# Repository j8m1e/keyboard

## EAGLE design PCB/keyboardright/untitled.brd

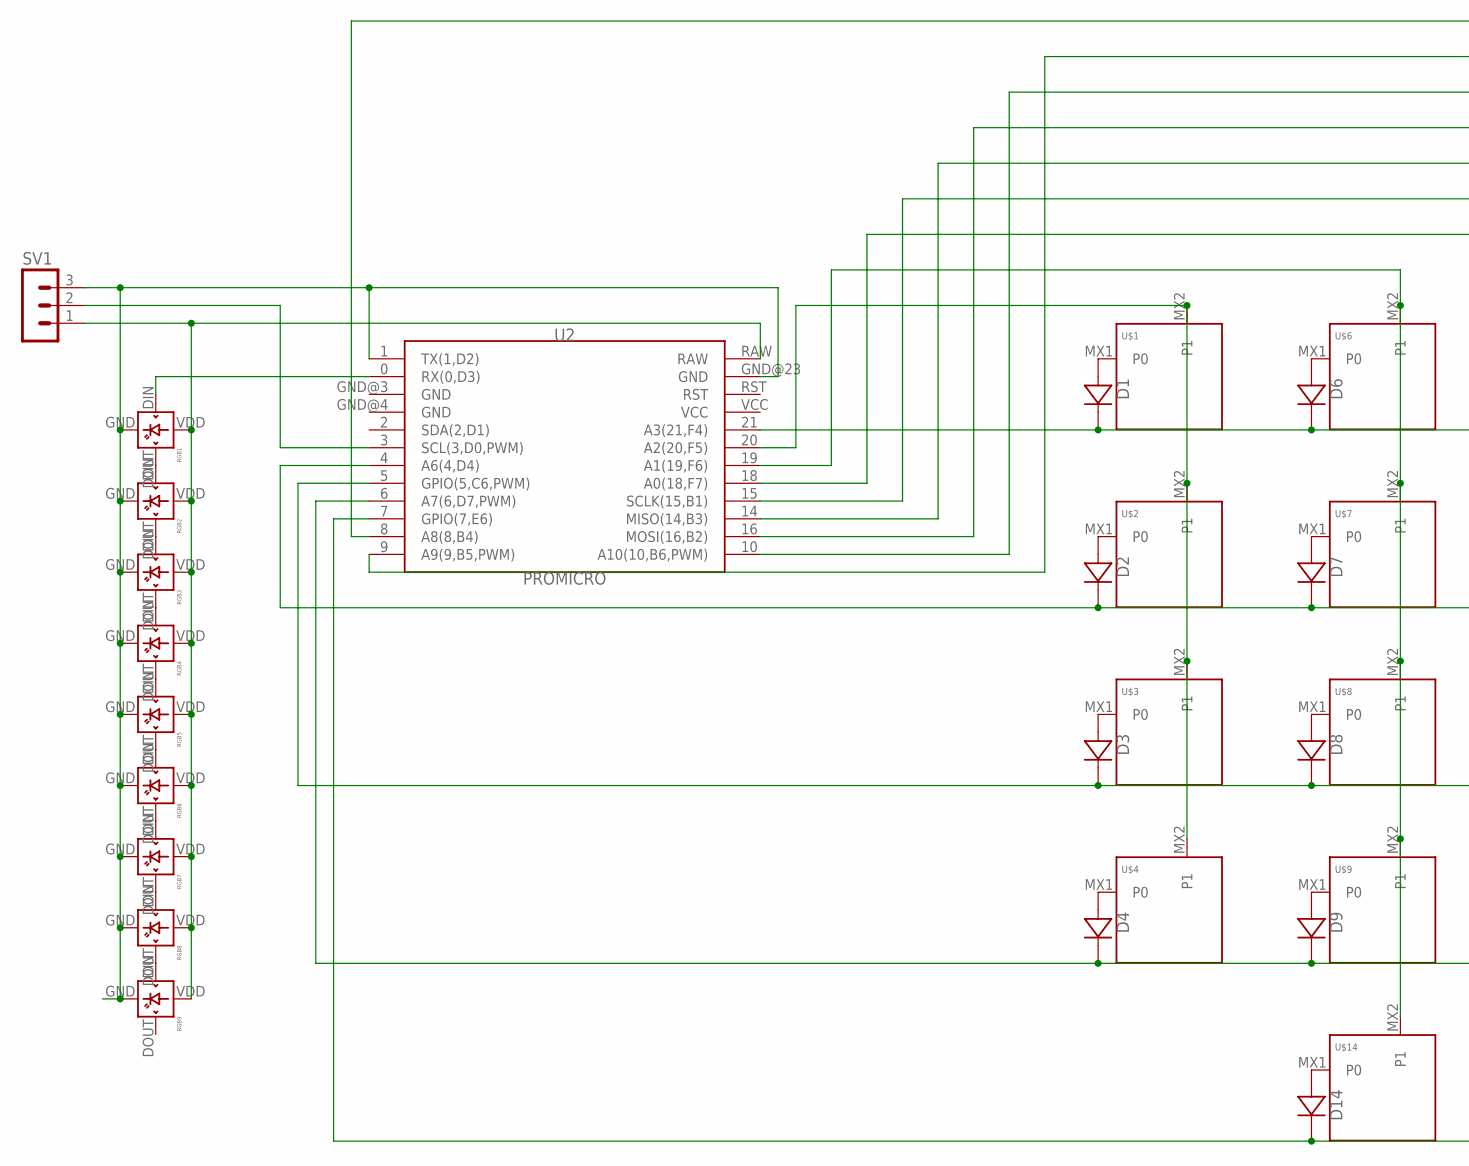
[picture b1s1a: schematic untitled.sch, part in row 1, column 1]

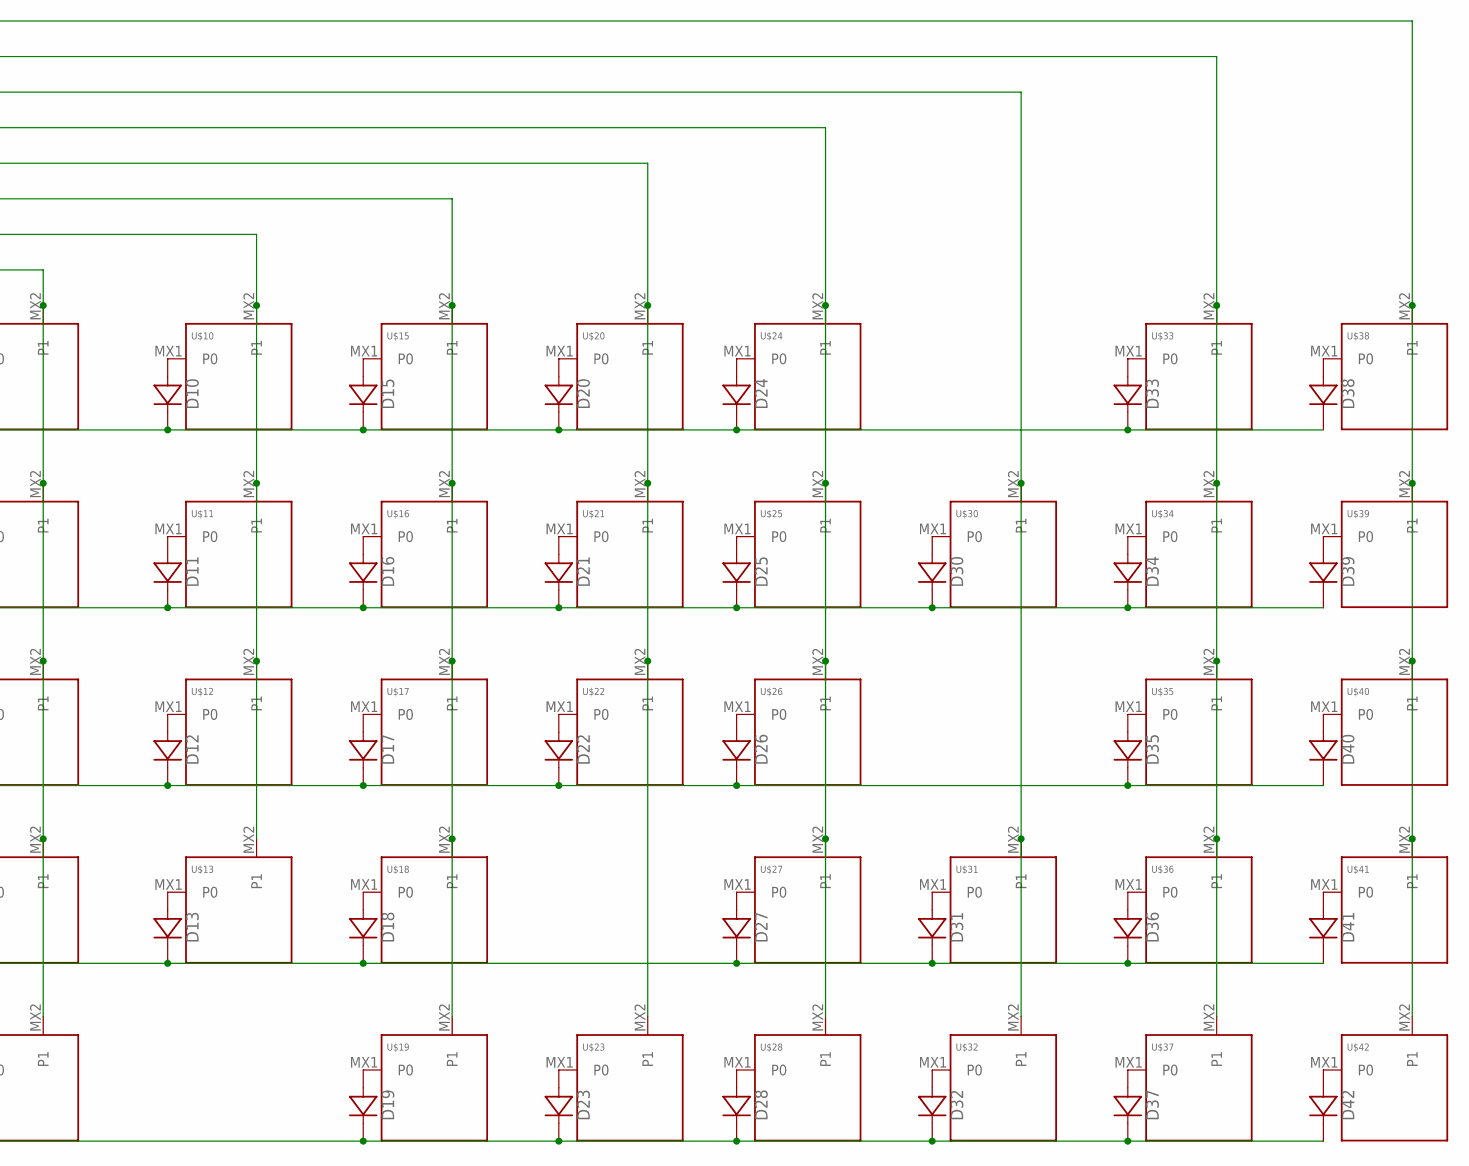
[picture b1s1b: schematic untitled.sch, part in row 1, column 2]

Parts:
D1, D2, D3, D4, D6, D7, D8, D9, D10, D11, D12, D13, D14, D15, D16, D17, D18, D19, D20, D21, D22, D23, D24, D25, D26, D27, D28, D30, D31, D32, D33, D34, D35, D36, D37, D38, D39, D40, D41, D42: DIODE-SOD-123; SOD-123
RGB1, RGB2, RGB3, RGB4, RGB5, RGB6, RGB7, RGB8, RGB9: WS2812B-MINI
SV1: MA03-1
U2: PROMICRO
U$1, U$2, U$3, U$4, U$6, U$7, U$8, U$9, U$10, U$11, U$12, U$13, U$14, U$15, U$16, U$17, U$18, U$19, U$20, U$21, U$22, U$23, U$24, U$25, U$26, U$27, U$28, U$30, U$31, U$32, U$33, U$34, U$35, U$36, U$37, U$38, U$39, U$40, U$41, U$42: KEYSWITCH-PLAIN-MX-1U; MX-1U

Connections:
unnamed: D1.A, U$1.MX1 (P0)
unnamed: D2.A, U$2.MX1 (P0)
unnamed: D3.A, U$3.MX1 (P0)
unnamed: D4.A, U$4.MX1 (P0)
unnamed: RGB1.DOUT, RGB2.DIN
unnamed: D6.A, U$6.MX1 (P0)
unnamed: D7.A, U$7.MX1 (P0)
unnamed: D8.A, U$8.MX1 (P0)
unnamed: D9.A, U$9.MX1 (P0)
unnamed: D10.A, U$10.MX1 (P0)
unnamed: D11.A, U$11.MX1 (P0)
unnamed: D12.A, U$12.MX1 (P0)
unnamed: D13.A, U$13.MX1 (P0)
unnamed: D14.A, U$14.MX1 (P0)
unnamed: D15.A, U$15.MX1 (P0)
unnamed: D16.A, U$16.MX1 (P0)
unnamed: D17.A, U$17.MX1 (P0)
unnamed: D18.A, U$18.MX1 (P0)
unnamed: D19.A, U$19.MX1 (P0)
unnamed: D20.A, U$20.MX1 (P0)
unnamed: D21.A, U$21.MX1 (P0)
unnamed: D22.A, U$22.MX1 (P0)
unnamed: D23.A, U$23.MX1 (P0)
unnamed: D24.A, U$24.MX1 (P0)
unnamed: D25.A, U$25.MX1 (P0)
unnamed: D26.A, U$26.MX1 (P0)
unnamed: D27.A, U$27.MX1 (P0)
unnamed: D28.A, U$28.MX1 (P0)
unnamed: RGB2.DOUT, RGB3.DIN
unnamed: D30.A, U$30.MX1 (P0)
unnamed: D31.A, U$31.MX1 (P0)
unnamed: D32.A, U$32.MX1 (P0)
unnamed: D33.A, U$33.MX1 (P0)
unnamed: D34.A, U$34.MX1 (P0)
unnamed: D35.A, U$35.MX1 (P0)
unnamed: D36.A, U$36.MX1 (P0)
unnamed: D37.A, U$37.MX1 (P0)
unnamed: D38.A, U$38.MX1 (P0)
unnamed: D39.A, U$39.MX1 (P0)
unnamed: D40.A, U$40.MX1 (P0)
unnamed: D41.A, U$41.MX1 (P0)
unnamed: D42.A, U$42.MX1 (P0)
unnamed: U2.20 (A2(20,F5)), U$1.MX2 (P1), U$2.MX2 (P1), U$3.MX2 (P1), U$4.MX2 (P1)
unnamed: U2.19 (A1(19,F6)), U$6.MX2 (P1), U$7.MX2 (P1), U$8.MX2 (P1), U$9.MX2 (P1), U$14.MX2 (P1)
unnamed: U2.18 (A0(18,F7)), U$10.MX2 (P1), U$11.MX2 (P1), U$12.MX2 (P1), U$13.MX2 (P1)
unnamed: U2.15 (SCLK(15,B1)), U$15.MX2 (P1), U$16.MX2 (P1), U$17.MX2 (P1), U$18.MX2 (P1), U$19.MX2 (P1)
unnamed: U2.14 (MISO(14,B3)), U$20.MX2 (P1), U$21.MX2 (P1), U$22.MX2 (P1), U$23.MX2 (P1)
unnamed: U2.16 (MOSI(16,B2)), U$24.MX2 (P1), U$25.MX2 (P1), U$26.MX2 (P1), U$27.MX2 (P1), U$28.MX2 (P1)
unnamed: U2.10 (A10(10,B6,PWM)), U$30.MX2 (P1), U$31.MX2 (P1), U$32.MX2 (P1)
unnamed: U2.9 (A9(9,B5,PWM)), U$33.MX2 (P1), U$34.MX2 (P1), U$35.MX2 (P1), U$36.MX2 (P1), U$37.MX2 (P1)
unnamed: D1.C, D6.C, D10.C, D15.C, D20.C, D24.C, D33.C, D38.C, U2.21 (A3(21,F4))
unnamed: D2.C, D7.C, D11.C, D16.C, D21.C, D25.C, D30.C, D34.C, D39.C, U2.4 (A6(4,D4))
unnamed: D3.C, D8.C, D12.C, D17.C, D22.C, D26.C, D35.C, D40.C, U2.5 (GPIO(5,C6,PWM))
unnamed: D4.C, D9.C, D13.C, D18.C, D27.C, D31.C, D36.C, D41.C, U2.6 (A7(6,D7,PWM))
unnamed: D14.C, D19.C, D23.C, D28.C, D32.C, D37.C, D42.C, U2.7 (GPIO(7,E6))
unnamed: U2.8 (A8(8,B4)), U$38.MX2 (P1), U$39.MX2 (P1), U$40.MX2 (P1), U$41.MX2 (P1), U$42.MX2 (P1)
unnamed: RGB3.DOUT, RGB4.DIN
unnamed: RGB4.DOUT, RGB5.DIN
unnamed: RGB5.DOUT, RGB6.DIN
unnamed: RGB6.DOUT, RGB7.DIN
unnamed: RGB7.DOUT, RGB8.DIN
unnamed: RGB8.DOUT, RGB9.DIN
unnamed: RGB1.VDD, RGB2.VDD, RGB3.VDD, RGB4.VDD, RGB5.VDD, RGB6.VDD, RGB7.VDD, RGB8.VDD, RGB9.VDD, SV1.1, U2.RAW
unnamed: RGB1.GND, RGB2.GND, RGB3.GND, RGB4.GND, RGB5.GND, RGB6.GND, RGB7.GND, RGB8.GND, RGB9.GND, SV1.3, U2.1 (TX(1,D2)), U2.GND@23 (GND)
unnamed: RGB1.DIN, U2.0 (RX(0,D3))
unnamed: SV1.2, U2.3 (SCL(3,D0,PWM))

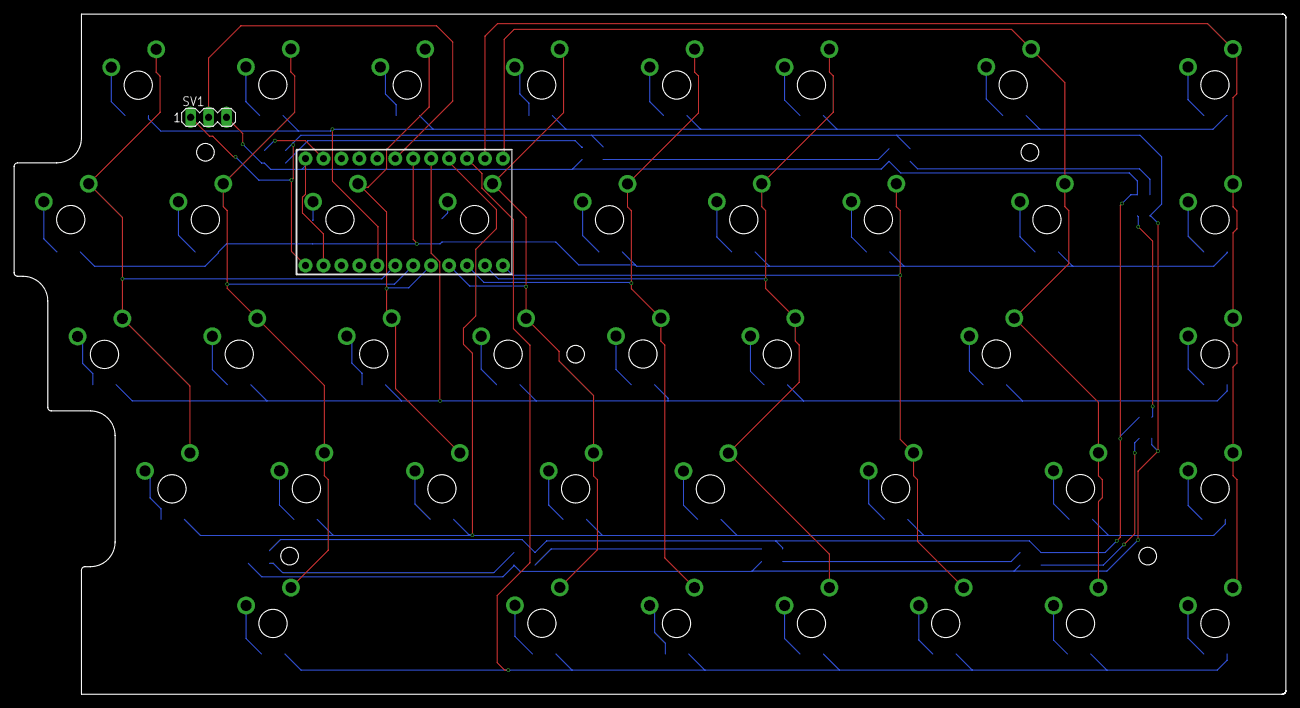
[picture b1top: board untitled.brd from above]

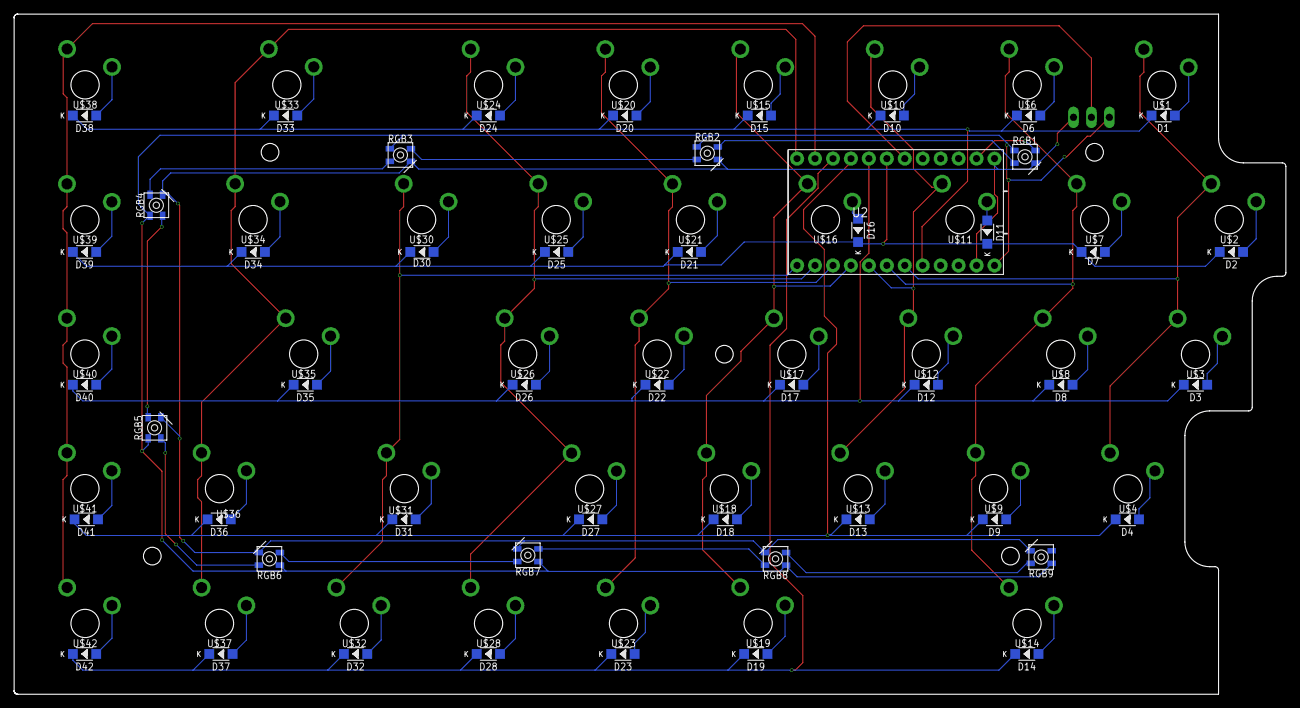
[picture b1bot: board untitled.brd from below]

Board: 2 copper layers, 180.0 x 96.2 mm, 91 parts (50 on the bottom side), 66 nets.

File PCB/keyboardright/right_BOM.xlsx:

Comment | Designator | Footprint | LCSC Part #（optional）
DIODE-SOD-123 | D1, D2, D3, D4, D6, D7, D8, D9, D10, D11, D12, D13, D14, D15, D16, D17, D18, D1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 | SOD-123
MA03-1 | SV1 | MA03-1
KEYSWITCH-PLAIN-MX-1U | U$1, U$2, U$3, U$4, U$6, U$7, U$8, U$9, U$10, U$11, U$12, U$13, U$14, U$15, U$1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 | MX-1U
PROMICRO | U2 | PROMICRO
WS2812B-MINI | RGB1, RGB2, RGB3, RGB4, RGB5, RGB6, RGB7, RGB8, RGB9 | WS2812B-MINI

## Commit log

2024-08-10 "updated ./quefrency.h"
2024-08-10 "updated ./readme.md"
2024-08-10 "updated ./info.json"
2024-08-10 "updated ./quefrency.c"
2024-08-10 "updated ./rules.mk"
2024-08-10 "updated ./keymaps/drashna_ms/config.h"
2024-08-10 "updated ./keymaps/default65macro/config.h"
2024-08-10 "updated ./config.h"
2024-08-10 "updated ./keymaps/default65macro/keymap.c"
2024-08-10 "updated ./keymaps/bramver/keymap.c"
2024-08-10 "updated ./keymaps/drashna_ms/keymap.c"
2024-08-10 "updated ./keymaps/drashna_ms/rules.mk"
2024-08-10 "updated ./keymaps/bramver/README.md"
2024-08-10 "updated ./keymaps/default65/keymap.c"
2024-08-10 "updated ./keymaps/bramver/config.h"
2024-08-10 "updated ./keymaps/default65/config.h"
2024-08-10 "updated ./keymaps/bramver/rules.mk"
2024-08-10 "updated ./keymaps/default/keymap.c"
2024-08-10 "updated ./keymaps/georgepetri/config.h"
2024-08-10 "updated ./keymaps/unausgeschlafen/readme.md"
2024-08-10 "updated ./keymaps/unausgeschlafen/rules.mk"
2024-08-10 "updated ./keymaps/kingwangwong/config.h"
2024-08-10 "updated ./keymaps/default/config.h"
2024-08-10 "updated ./keymaps/georgepetri/keymap.c"
2024-08-10 "updated ./keymaps/unausgeschlafen/keymap.c"
2024-08-10 "updated ./keymaps/kingwangwong/keymap.c"
2024-08-10 "updated ./keymaps/unausgeschlafen/config.h"
2024-08-10 "updated ./keymaps/bcat/keymap.c"
2024-08-10 "updated ./keymaps/bjohnson/rules.mk"
2024-08-10 "updated ./keymaps/bcat/readme.md"
2024-08-10 "updated ./keymaps/bjohnson/config.h"
2024-08-10 "updated ./keymaps/bcat/rules.mk"
2024-08-10 "updated ./keymaps/georgepetri/rules.mk"
2024-08-10 "updated ./rev1/rev1.h"
2024-08-10 "updated ./rev1/config.h"
2024-08-10 "updated ./keymaps/bcat/config.h"
2024-08-10 "updated ./keymaps/georgepetri/readme.md"
2024-08-10 "updated ./keymaps/bjohnson/keymap.c"
2024-08-10 "updated ./rev1/rev1.c"
2024-08-10 "updated ./rev1/rules.mk"
2024-08-10 "updated ./qmk/config.h"
2024-08-10 "updated ./qmk/keymaps/drashna_ms/keymap.c"
2024-08-10 "updated ./qmk/info.json"
2024-08-10 "updated ./qmk/keymaps/drashna_ms/config.h"
2024-08-10 "updated ./qmk/keymaps/default65macro/config.h"
2024-08-10 "updated ./qmk/quefrency.h"
2024-08-10 "updated ./qmk/quefrency.c"
2024-08-10 "updated ./qmk/keymaps/default65macro/keymap.c"
2024-08-10 "updated ./qmk/rules.mk"
2024-08-10 "updated ./qmk/keymaps/default65/keymap.c"
2024-08-10 "updated ./qmk/keymaps/bramver/keymap.c"
2024-08-10 "updated ./qmk/keymaps/bramver/config.h"
2024-08-10 "updated ./qmk/keymaps/default/keymap.c"
2024-08-10 "updated ./qmk/keymaps/unausgeschlafen/readme.md"
2024-08-10 "updated ./qmk/keymaps/default65/config.h"
2024-08-10 "updated ./qmk/keymaps/unausgeschlafen/config.h"
2024-08-10 "updated ./qmk/keymaps/drashna_ms/rules.mk"
2024-08-10 "updated ./qmk/keymaps/bramver/README.md"
2024-08-10 "updated ./qmk/keymaps/bramver/rules.mk"
2024-08-10 "updated ./qmk/keymaps/default/config.h"
2024-08-10 "updated ./qmk/keymaps/unausgeschlafen/keymap.c"
2024-08-10 "updated ./qmk/keymaps/bjohnson/keymap.c"
2024-08-10 "updated ./qmk/keymaps/kingwangwong/config.h"
2024-08-10 "updated ./qmk/keymaps/bjohnson/rules.mk"
2024-08-10 "updated ./qmk/keymaps/bcat/config.h"
2024-08-10 "updated ./qmk/keymaps/georgepetri/rules.mk"
2024-08-10 "updated ./qmk/keymaps/georgepetri/config.h"
2024-08-10 "updated ./qmk/keymaps/kingwangwong/keymap.c"
2024-08-10 "updated ./qmk/keymaps/bjohnson/config.h"
2024-08-10 "updated ./qmk/keymaps/georgepetri/readme.md"
2024-08-10 "updated ./qmk/keymaps/georgepetri/keymap.c"
2024-08-10 "updated ./qmk/keymaps/unausgeschlafen/rules.mk"
2024-08-10 "updated ./design phase/Untitled v2.dwg"
2024-08-10 "updated ./qmk/rev1/config.h"
2024-08-10 "updated ./qmk/keymaps/bcat/rules.mk"
2024-08-10 "updated ./design phase/Untitled v0.step"
2024-08-10 "updated ./design phase/keyboard-layout.json"
2024-08-10 "updated ./qmk/keymaps/bcat/readme.md"
2024-08-10 "updated ./qmk/keymaps/bcat/keymap.c"
2024-08-10 "updated ./qmk/rev1/rev1.h"
2024-08-10 "updated ./design phase/kbd67.json"
2024-08-16 "updated ./PCB/keyboardleft/untitled.b#3"
2024-08-16 "updated ./PCB/plate.dxf"
2024-08-16 "updated ./PCB/cut.dxf"
2024-08-16 "updated ./PCB/keyboard-layout.json"
2024-08-16 "updated ./PCB/keyboardleft/untitled.b#4"
2024-08-16 "updated ./PCB/keyboardleft/untitled.s#2"
2024-08-16 "updated ./PCB/keyboardleft/untitled.s#4"
2024-08-16 "updated ./PCB/keyboardleft/untitled.b#5"
2024-08-16 "updated ./PCB/keyboardleft/dxfimp.scr"
2024-08-16 "updated ./PCB/keyboardleft/untitled.s#3"
2024-08-16 "updated ./PCB/keyboardleft/untitled.brd"
2024-08-16 "updated ./PCB/keyboardleft/left.zip"
2024-08-16 "updated ./PCB/keyboardleft/untitled.b#2"
2024-08-16 "updated ./PCB/keyboardleft/untitled.b#7"
2024-08-16 "updated ./PCB/keyboardleft/untitled.s#5"
2024-08-16 "updated ./PCB/keyboardleft/left_CPL.xlsx"
2024-08-16 "updated ./PCB/keyboardleft/left_BOM.xlsx"
2024-08-16 "updated ./PCB/keyboardleft/untitled.b#6"
2024-08-16 "updated ./PCB/keyboardright/untitled.b#3"
2024-08-16 "updated ./PCB/keyboardright/right.zip"
2024-08-16 "updated ./PCB/keyboardleft/untitled.b#8"
2024-08-16 "updated ./PCB/keyboardleft/untitled.s#1"
2024-08-16 "updated ./PCB/keyboardright/untitled.b#4"
2024-08-16 "updated ./PCB/keyboardright/dxfimp.scr"
2024-08-16 "updated ./PCB/keyboardleft/untitled.b#1"
2024-08-16 "updated ./PCB/keyboardleft/eagle.epf"
2024-08-16 "updated ./PCB/keyboardleft/untitled.sch"
2024-08-16 "updated ./PCB/keyboardright/untitled.s#4"
2024-08-16 "updated ./PCB/keyboardright/right_CPL.xlsx"
2024-08-16 "updated ./PCB/keyboardright/untitled.s#3"
2024-08-16 "updated ./PCB/keyboardright/untitled.b#9"
2024-08-16 "updated ./PCB/keyboardright/untitled.s#2"
2024-08-16 "updated ./PCB/keyboardright/eagle.epf"
2024-08-16 "updated ./PCB/keyboardright/untitled.s#5"
2024-08-16 "updated ./PCB/keyboardright/untitled.b#7"
2024-08-16 "updated ./PCB/keyboardright/untitled.b#2"
2024-08-16 "updated ./PCB/keyboardright/untitled.b#5"
2024-08-16 "updated ./PCB/keyboardright/untitled.brd"
2024-08-16 "updated ./PCB/keyboardright/untitled.b#6"
2024-08-16 "updated ./PCB/keyboardright/right_BOM.xlsx"
2024-08-16 "updated ./PCB/keyboardright/untitled.s#6"
2024-08-16 "updated ./PCB/keyboardright/untitled.sch"
2024-08-16 "updated ./PCB/keyboardright/untitled.b#8"
2024-08-16 "updated ./PCB/keyboardright/untitled.b#1"
2024-08-16 "updated ./PCB/keyboardright/untitled.s#1"
